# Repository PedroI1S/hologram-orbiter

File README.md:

# Hologram Orbiter

Display volumétrico por persistência de visão (POV) com três painéis de LEDs.
Ponto de projeto: raio médio **100 mm**, **1800 RPM**, 29 LEDs por painel e 180
colunas angulares (90 passagens por segundo; desempenho óptico depende de
firmware e ensaio).

**Versão vigente: v4.0 (14/11/2026)** — promove a base suspensa em paralelogramo
travável + aranha reforçada (`3.1-P.2`) e o motor **`AX-2810Q 750KV`** ao plano
principal. Os documentos e o pacote CAD da `v3.0` (base rígida + `A2212 920KV`)
foram arquivados em [`legado/v3.0/`](legado/v3.0/).

## Estado em 14/11/2026

> **PROVISÓRIO — não liberado para girar o rotor completo nem para fabricação
> definitiva dos painéis.**

- **CAD e física v4.0 regenerados (`69/69` critérios de aceitação):**
  - **Base suspensa em paralelogramo travável (PETG):** palco pendurado em 8
    hastes de `1,5 × 1,5 mm` (translação prevista em `4,38 Hz` / crítica
    `~263 RPM`), trava reversível 4 + 4 para operar em modo rígido e bandeja
    provisória para amortecimento viscoso com óleo de silicone `10 000 cSt`.
  - **Aranha reforçada (PETG):** aleta vertical em **D** + alma em perfil de asa
    invertido até o ombro (`r = 74 mm`), baia ampliada para **`Ø80/84 × 47 mm`**
    com prateleira em `Z = 28 mm` para futura placa própria.
  - **Motor e fixação (`AX-2810Q 750KV`):** medidas de bancada de `13/11/2026`
    incorporadas (assento serrilhado `Ø13` a `29 mm` da base, trecho liso
    `Ø4 × 5 mm` com bucha `Ø6`, rosca `M4 × 10`, porca `DIN 985 M4` + arruela
    `DIN 9021 M4`, furos de base em cruz `16/19 mm`, fios `Ø3,0 mm` em ganchos na
    torre, chapa `R01` com alívio `Ø11`). Réplica provisória `R01P` em PLA
    disponível até o corte em alumínio 2 mm.
- **Eletrônica e acionamento em bancada:**
  - **SPI Quad** montada ponto a ponto em placa perfurada
    ([`MONTAGEM-PONTO-A-PONTO.md`](eletronica/interface/MONTAGEM-PONTO-A-PONTO.md)),
    4 condutores por painel (`+5 V`, `GND`, `CLK`, `DATA`), em teste de bancada
    com [`firmware/teste-fitas-c3/`](firmware/teste-fitas-c3/).
  - **ESC + `AX-2810Q`:** gravados em `13/11/2026` (`Startup Power = 0,50`,
    `Demag = High`, `Brake on stop = On`; ver
    [`esc_blheli_s_2026-11-13/`](esc_blheli_s_2026-11-13/registro.md)). Sentido
    de giro anti-horário, calibração do pulso por tacômetro, grampo/resistor de
    descarga no barramento do ESC e ajustes de rampa no firmware da base ainda
    pendentes antes de girar com rotor.
- **Pendências principais antes de girar:** fechar medição da altura do corpo do
  `AX-2810Q` (`26 mm` de catálogo), imprimir peças e executar o ensaio de
  impacto **`C0`** da suspensão (modo travado e modo solto), reconciliar massa
  real pesada até o teto provisório de **`420 g`** e cumprir os bloqueadores do
  plano 04.

Os relatórios automáticos são a referência da execução atual do CAD:

- [Aceitação geométrica (69/69)](Hologram_Orbiter_v4/reports/ACEITACAO.md)
- [Validação, massas CAD e acionamento](Hologram_Orbiter_v4/reports/RELATORIO_VALIDACAO.md)
- [Cálculos reproduzíveis](Hologram_Orbiter_v4/reports/FISICA.json)
- [Revisões históricas (v3.0)](revisoes/LEIA-ME.md)

## Números de projeto (v4.0)

| Grandeza | Valor e condição |
|---|---|
| Rotação / velocidade angular | **1800 RPM** / 188,496 rad/s (30 rps, 90 Hz de imagem) |
| Cilindro de imagem | **Ø208 × 201 mm**, 29 LEDs × 180 colunas |
| Motor / acionamento | **AX-2810Q 750KV** (`R_ef = 0,225 Ω`, `Kt = 12,73 mN·m/A`) / **ESC LittleBee Spring 20A** |
| Corrente de regime prevista | **4,04 A** de fase (**3,62 A** melhor caso); **14,81 W** na fonte (`1,48 A` a 10 V, `1,23 A` a 12 V, `η_ESC = 95%`) |
| Temperatura prevista | **40,3 °C** (`37,8 °C` melhor caso) sob `Rth = 3,5 K/W`; limite `< 55 °C` (medir no Bloqueador B) |
| Fonte do ESC | **10–12 V** com limite de **30 A**; **grampo ou resistor de descarga obrigatório** (`Brake on stop = On`) |
| Perfil de partida (chute legado, não aprovado) | Chute de `1400 µs`: no modelo médio para o `AX-2810Q`, `16,37–19,65 A` de fase parado e pico de `1680 RPM` (10 V) / `1959 RPM` (12 V); excede Bloqueador D e exige revisão + rampa `≥ 300 RPM/s` pela crítica `~263 RPM` |
| Esticada a 2000 RPM | `4,99 A` / `20,63 W` / `47,0 °C` estimados; **não liberada** (3× próximo do modo ~89 Hz e > 20 W) |
| Massa do rotor | Teto provisório **420 g**; subtotal nominal **352,14 g** (reconciliar chicotes 4 fios e pesar) |
| Carga radial no painel | **158,1 N** a `44,5 g` (`159,9 N` no teto de `45 g`) |
| Energia cinética | **27,5–27,6 J** no rotor (`J = 1,55 g·m²` assumido); **7,9 J** (`18,9 m/s`) por painel solto |
| Desbalanceamento de referência | **8,4 g·mm** (ref. G6.3 a 1800 RPM; recalcular com massa pesada e balancear em 2 planos) |
| Modos da suspensão (estimativa `E = 1900 MPa`) | Translação **4,38 Hz** (**263 RPM**); *yaw* **12,66 Hz** (**759 RPM**, evitar banda `760–870 RPM`); combinado balanço+torre **89,3 Hz** (3× em `~1786 RPM`); balanço **105,2 Hz**; flambagem `36,3 N` |

A PCB KiCad de interface `r0.2` está preservada em [`eletronica/interface/`](eletronica/interface/README.md)
como referência de projeto; para o protótipo atual sem PCB fabricada, seguir o
roteiro de soldagem em perfboard [`MONTAGEM-PONTO-A-PONTO.md`](eletronica/interface/MONTAGEM-PONTO-A-PONTO.md).

## Documentos vigentes (v4.0)

| Uso | Arquivo |
|---|---|
| Cotas, geometria e memória de cálculo | [`01-ESPECIFICACAO-CAD-v4.0.md`](01-ESPECIFICACAO-CAD-v4.0.md) |
| Fases e portões `G0`–`G5` | [`02-PLANO-DE-PROJETO-v4.0.md`](02-PLANO-DE-PROJETO-v4.0.md) |
| Componentes, ferragens e instrumentos | [`03-LISTA-DE-COMPONENTES-v4.0.md`](03-LISTA-DE-COMPONENTES-v4.0.md) |
| Critérios físicos de aceite (`C0`, `A`–`E`) | [`04-PLANO-DE-ENSAIOS-v4.0.md`](04-PLANO-DE-ENSAIOS-v4.0.md) |
| Eletrônica **SPI Quad**, ESC e firmware | [`05-ESQUEMA-ELETRICO-v4.0.md`](05-ESQUEMA-ELETRICO-v4.0.md) |
| O que ainda falta | [`06-PENDENCIAS-ABERTAS-v4.0.md`](06-PENDENCIAS-ABERTAS-v4.0.md) |
| Medições, vocabulário e premissas | [`07-GLOSSARIO-E-PREMISSAS.md`](07-GLOSSARIO-E-PREMISSAS.md) |
| CAD, 16 STLs, DXF e guias de impressão/montagem | [`Hologram_Orbiter_v4/README.md`](Hologram_Orbiter_v4/README.md) |
| Firmware (base ESC + bancada SPI Quad C3) | [`firmware/README.md`](firmware/README.md) |
| Interface SPI Quad (perfboard e KiCad ref.) | [`eletronica/interface/README.md`](eletronica/interface/README.md) |
| Arquivo morto (`v3.0` e `v2.1`) | [`legado/LEIA-ME.md`](legado/LEIA-ME.md) |

Parâmetros do CAD governam cotas, a especificação governa requisitos e o plano
de ensaios governa aceite físico. Divergências devem ser corrigidas na fonte,
nunca escolhendo o número mais favorável. A [proposta e suas apresentações](proposta/README.md)
conservam os números históricos da proposta inicial.

Sentido de giro: **anti-horário visto de cima**; bordo de ataque em `+y` local.
Balança de `0,01 g`, contenção física, grampo no barramento do ESC, base
grampeada e operação remota são obrigatórios em ensaio.

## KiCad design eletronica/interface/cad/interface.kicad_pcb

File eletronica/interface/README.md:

# PCB de interface do rotor — r0.2

Placa de sinais em 15 × 20 mm, duas camadas, com montagem SMD no topo. Esta revisão implementa a arquitetura da proposta SPI quad lembrada pelo usuário: CLK comum, três DATA independentes e alimentação dos painéis em estrela externa. É um protótipo para orçamento e posterior ensaio, não uma eletrônica já qualificada em bancada.

## Arquivos para orçamento e revisão

- `fabricacao/gerbers/`: cobre, máscaras, serigrafias, pasta e furação exportados pelo KiCad.
- `fabricacao/Gerbers_Orbiter_r02.zip`: enviar ao campo de Gerber do fornecedor.
- `fabricacao/BOM.csv`: lista de compra e montagem, com MPN e quantidade por placa.
- `fabricacao/BOM-JLCPCB.csv`: correspondência de componentes para a JLCPCB.
- `fabricacao/PickAndPlace.csv`: coordenadas e rotações dos 17 SMDs.
- `fabricacao/mapa-fios.csv`: correspondência dos 19 pontos numerados com os sinais.
- `fabricacao/LEIA-ME-COTACAO.md`: requisitos para a fabricante, incluindo painelização e montagem.
- `fabricacao/Pacote_Orbiter_r02.zip`: conjunto para compartilhar com o fornecedor, incluindo fonte CAD e relatórios.
- `cad/interface.kicad_pro`, `cad/interface.kicad_sch`, `cad/interface.kicad_pcb`: projeto editável e bibliotecas locais.
- `reports/`: verificações, esquema exportado em SVG, PCB e molde físico 1:1.

A placa nua é cotada pelo Gerber; a montagem exige também BOM e Pick & Place. Conferir o preview do fornecedor, especialmente o pino 1 de U1 e as rotações. Códigos de componentes cadastrados não significam estoque reservado ou ausência de taxas adicionais.

## Circuito

| Função | Ligação |
|---|---|
| CLK comum | GPIO4 → U1 entrada 2 / saída 3 → R6, R10, R11 de 33 Ω → CLK de cada painel |
| DATA painel 1 | GPIO6 → U1 entrada 5 / saída 6 → R7 de 0 Ω → painel 1 |
| DATA painel 2 | GPIO5 → U1 entrada 9 / saída 8 → R12 de 0 Ω → painel 2 |
| DATA painel 3 | GPIO7 → U1 entrada 12 / saída 11 → R13 de 0 Ω → painel 3 |
| Habilitação do buffer | U1 pinos 1, 4, 10 e 13 ao GND |
| Repouso no reset | R1, R2, R8, R9: 10 kΩ de cada entrada digital ao GND |
| Alimentação de U1 | pino 14 em 5 V, pino 7 em GND; C1 100 nF junto ao CI e C2 1 µF local |
| Hall | A3144 externo em 5 V; R3 10 kΩ da saída a 3V3; leitura em GPIO3 |
| Bateria | R4 150 kΩ de VBAT_SW ao ADC; R5 47 kΩ ao GND; C3 100 nF ao GND; leitura em GPIO0 |

U1: SN74AHCT125DR, SOIC-14, entrada TTL e saída em 5 V. Não substituir por HC. Quatro canais usados; não sobram canais para clocks independentes. Um clock aciona três ramos com resistores série individuais, como na proposta local. Os resistores de DATA em 0 Ω permitem ajuste em bancada.

GPIO10 fica reservado para a quarta linha do periférico quad, sem fio na interface. As linhas DATA **não são unidas entre si**; cada painel recebe seus próprios bits. Saídas superiores das fitas ficam sem retorno à interface.

O ADC nominal vale 1,384 V a 5,8 V e 1,718 V a 7,2 V. Calibrar no firmware. O filtro deve permanecer próximo ao ADC eletricamente; manter o fio curto e acrescentar/reposicionar o capacitor junto ao C3 se a integração exigir. Este divisor mede a tensão e não desconecta a bateria.

## Fiação e alimentação

| Grupo funcional | Pinos |
|---|---|
| J1 — C3 | 1:5V; 2:GND; 3:3V3 vindo do C3; 4:GPIO4; 5:GPIO6; 6:GPIO3; 7:GPIO0; 8:GPIO5; 9:GPIO7 |
| J2 — Hall | 1:5V; 2:GND; 3:saída Hall |
| J3 — painel 1 | 1:CLK; 2:DATA painel 1 |
| J5 — painel 2 | 1:CLK; 2:DATA painel 2 |
| J6 — painel 3 | 1:CLK; 2:DATA painel 3 |
| J4 — bateria | 1:VBAT_SW, após chave/fusível e antes do buck |

Os grupos J representam pontos **distribuídos** pela placa, não headers comerciais contíguos. A numeração física 01–19 está na serigrafia inferior e no `mapa-fios.csv`. Os fios entram em furos metalizados de 0,5 mm; usar AWG28 nos sinais e na pequena alimentação da interface, conferindo o fio real. Fazer alívio mecânico. A ordem de J2 não representa a ordem dos terminais do sensor TO-92: conferir o componente real.

```
bateria + → fusível → chave → VBAT_SW → buck IN+
bateria - → GND comum / buck IN-
buck OUT+ → estrela 5V → painel 1+, painel 2+, painel 3+, C3 5V, interface 5V
buck OUT- → estrela GND → painel 1-, painel 2-, painel 3-, C3 GND, interface GND
1000 µF externo entre 5V e GND, no cubo
```

Cada painel recebe quatro fios: 5 V e GND pela distribuição de potência; CLK e seu DATA pela interface. Não passar os amperes dos LEDs pelas trilhas desta placa ou pelo fio fino de referência GND. O 5V do C3 recebe uma derivação externa própria; J1.1 não é um caminho de potência em série para o C3.

Chave, fusível, conector de balanceamento, buck e capacitor de 1000 µF continuam externos. É uma mudança de divisão física em relação à reserva antiga, que listava esses itens dentro de 15 × 20 sem modelos definidos. A acomodação e retenção desses componentes precisam ser verificadas no conjunto. Selecionar chave/fusível pela corrente DC real; não usar chave de sinal sem capacidade adequada para alimentar o buck. O buck real ainda precisa de qualificação ao longo da descarga da bateria.

> **Sem PCB:** a placa r0.2 não será fabricada. Para a montagem soldada à mão,
> com apenas o U1 já fixado, seguir [MONTAGEM-PONTO-A-PONTO.md](MONTAGEM-PONTO-A-PONTO.md)
> (mesmo circuito, com o envelope, o peso e a sequência de solda revistos).

## Encaixe

Centro no rotor `(27; 5) mm`, com cantos `(19,5; -5)` a `(34,5; 15)`. Na **v4.0**, a baia foi ampliada para **`Ø80` interno (`r = 40 mm`) / `Ø84` externo × `47 mm`**, deixando folga radial nominal de **`2,38 mm`** até o canto mais externo (`r = 37,62 mm`). *(Nos relatórios preservados da revisão `r0.2` / `v3.0`, como `reports/geometry.json`, a referência anterior era `r = 39 mm` / `1,38 mm`; o diagrama `reports/encaixe-baia.svg` já foi atualizado para `Ø80 mm`. Acima do berço da bateria, a prateleira em `Z = 28 mm` reserva espaço para uma eventual placa própria futura.)*

Furos de `2,2 mm` em `(2; 2)`, `(13; 2)`, `(13; 18)`, `(2; 18)` relativos ao canto da PCB. São os centros dos quatro pilares existentes no CAD. Cabeças até `Ø3,5 mm`, sem arruelas maiores; confirmar rosca e retenção nos pilares reais. A área das cabeças foi reservada também contra cobre/trilhas.

Face inferior da PCB a `Z = 6 mm`. Com FR4 de `1,6 mm` e SOIC de até aproximadamente `1,75 mm`, a pilha eletrônica fica abaixo do envelope anterior de `8 mm`. Fios e soldas não estão incluídos nessa comprovação nominal. Manter as pontas inferiores curtas para não obstruir chicotes sob a placa. O molde `reports/molde-1-para-1.svg` deve ser impresso a 100%; conferir a barra de `50 mm` antes de testar.

## Verificação e limites

Os resultados da revisão `r0.2` ficam em [`reports/VALIDACAO.md`](reports/VALIDACAO.md): zero violações ERC/DRC, zero conexões abertas e zero divergências de paridade no KiCad 10.0.7. Há conferência independente de geometria, continuidade entre camadas, folgas de cobre e equivalência de pinos entre tabela elétrica, esquemático e PCB. O DRC/ERC do KiCad e os arquivos exportados são verificados antes do empacotamento.

Isso não demonstra integridade dos sinais nos fios reais. Com rotor parado, verificar três padrões independentes, ordem de bits do SPI quad, clock na entrada das três fitas, funcionamento do Hall e leitura da bateria (ver [`firmware/teste-fitas-c3/`](../../firmware/teste-fitas-c3/)). Começar com alimentação limitada e obedecer ao teto provisório de corrente/brilho do esquema 05. Se um driver de clock para três ramos não bastar, será necessário rever hardware/clock; esta placa não reserva um segundo CI.

Ao programar o C3, confirmar o circuito da Super Mini real antes de alimentar simultaneamente por USB e buck; evitar realimentar fontes. Mudanças de massa/fiação exigem nova pesagem e balanceamento. Nenhuma pendência mecânica do rotor é encerrada pela interface.

## Reprodução

Os scripts em `scripts/` geram e verificam o projeto KiCad; as ferramentas são KiCad CLI, Python com `sexpdata`/`shapely` e Freerouting 2.1.0 em Java 21. O gerador de posicionamento não preserva edições manuais: usar o CAD final (`Hologram_Orbiter_v4/CAD/parameters.json`) como fonte ao alterar a placa e regenerar as saídas da revisão modificada.

## Referências

- [Esquema vigente (v4.0)](../../05-ESQUEMA-ELETRICO-v4.0.md): topologia SPI Quad vigente (4 fios por painel), alimentação, pinagem e requisitos de ensaio.
- [Montagem ponto a ponto (perfboard ativa)](MONTAGEM-PONTO-A-PONTO.md): roteiro prático em execução para o protótipo sem PCB fabricada.
- [Proposta SPI quad](../../revisoes/2026-09-21-PROPOSTA-SPI-QUAD.md): proposta original adotada na revisão e promovida na v4.0.
- [TI — SN74AHCT125](https://www.ti.com/lit/ds/symlink/sn74ahct125.pdf): pinagem, níveis e encapsulamento.
- [Espressif — checklist C3](https://docs.espressif.com/projects/esp-hardware-design-guidelines/en/latest/esp32c3/schematic-checklist.html): recomendação de filtro no ADC.

Para reexportar o CAD final sem regenerar o posicionamento: `python scripts/export_manufacturing.py --kicad-cli /caminho/kicad-cli` (KiCad 10 e dependências de `scripts/requirements.txt`).

Revisão de compra em 30/10: [BOM otimizada para JLCPCB](fabricacao/BOM-JLCPCB-otimizada.csv), com seis grupos Basic e substituto X7R 25 V para C2. Ver [substituições e consulta de estoque](reports/REVISAO-BOM-JLCPCB.md). Gerbers e Pick & Place permanecem os da PCB r0.2.

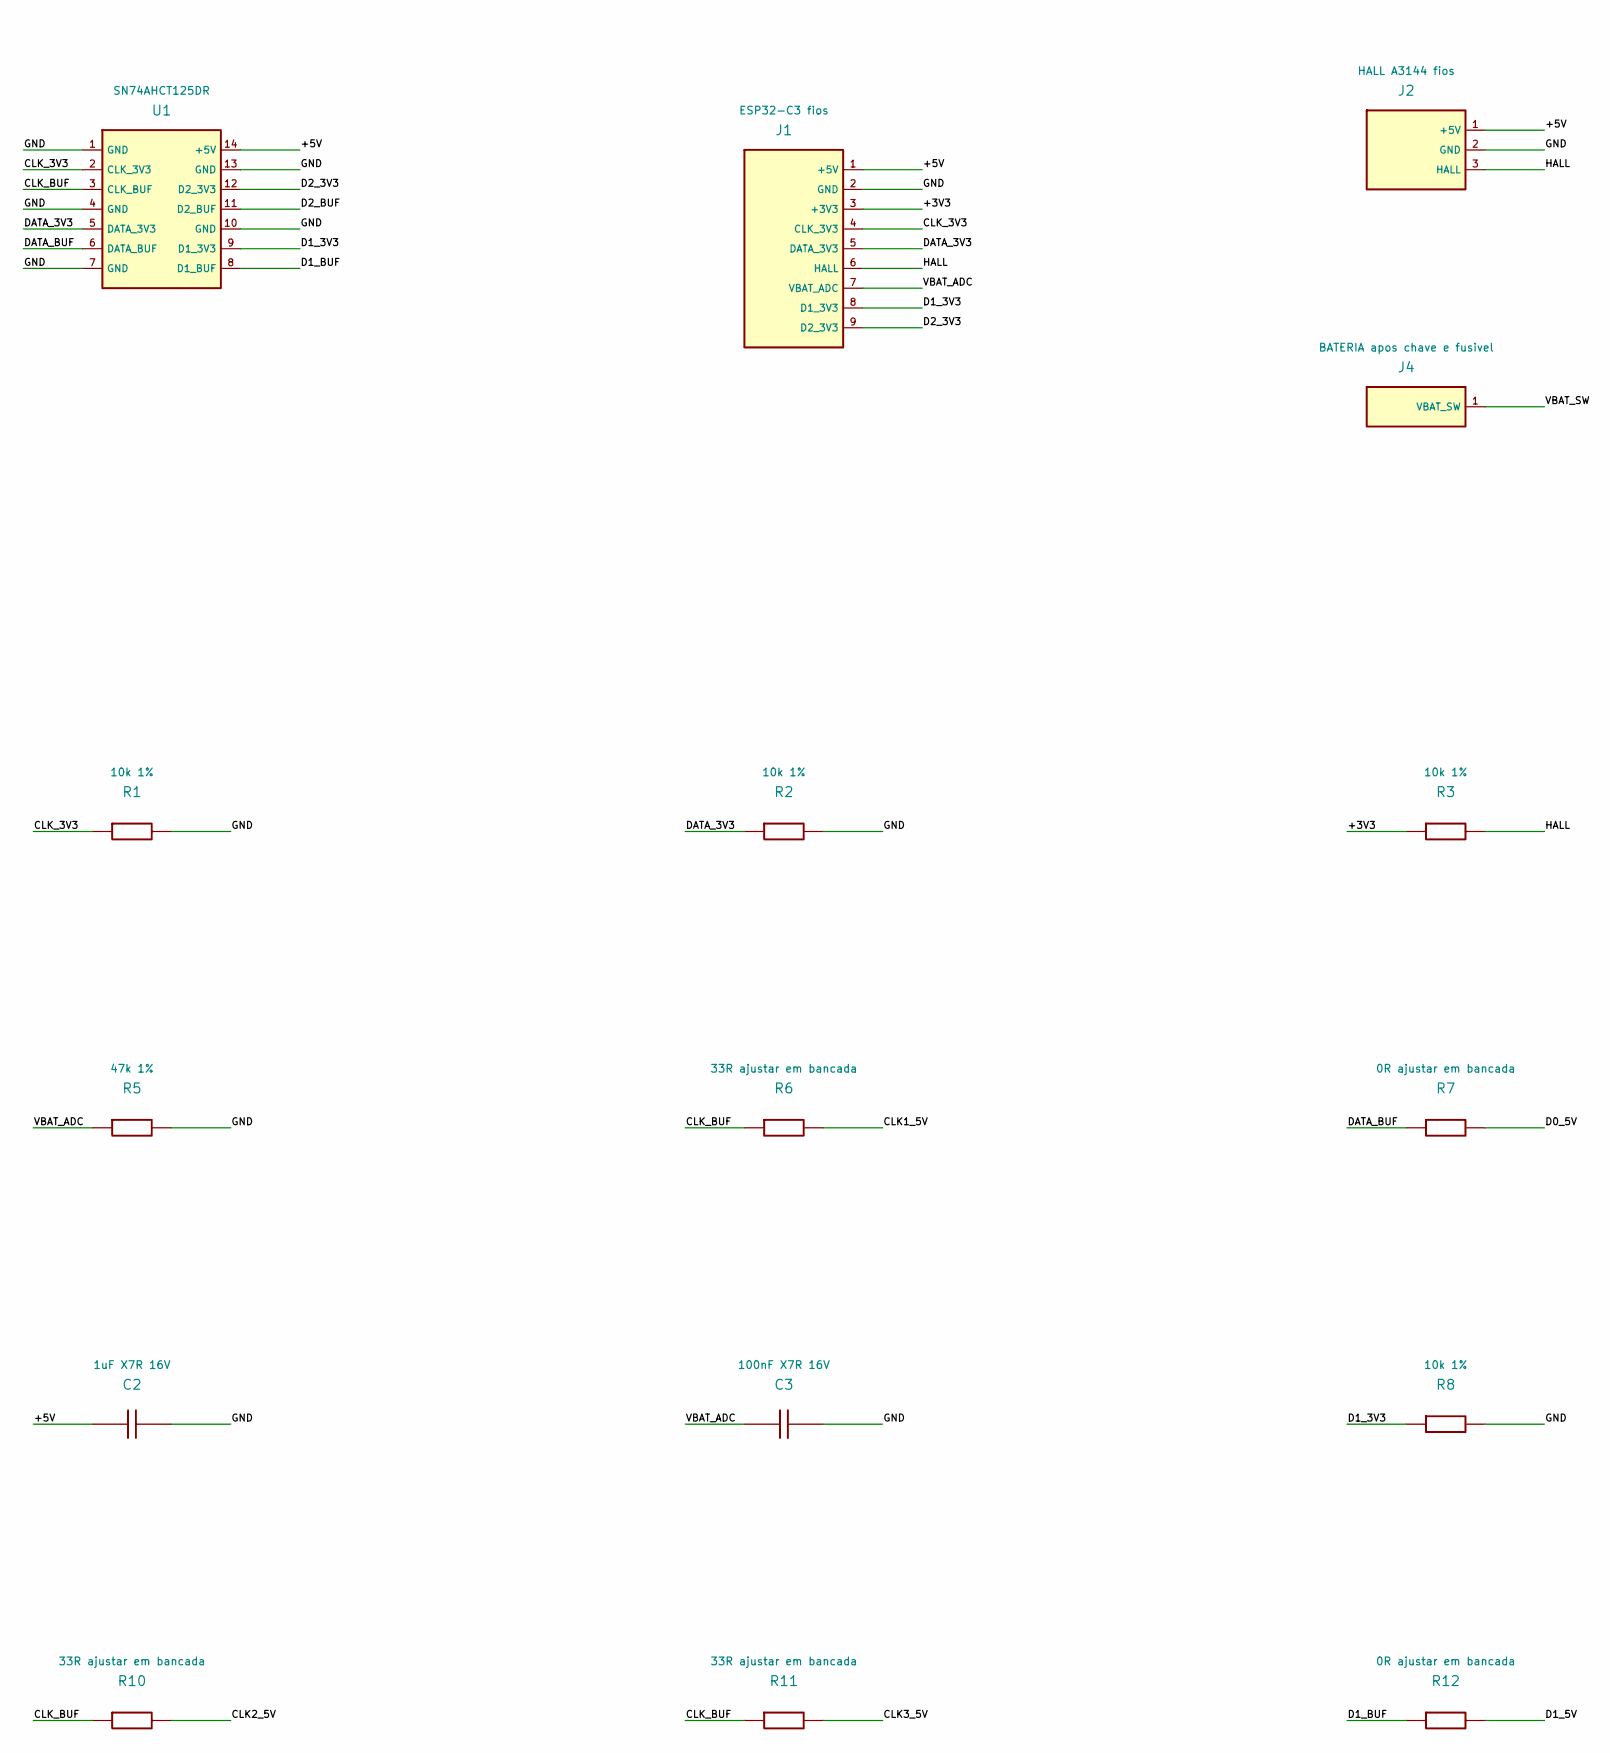
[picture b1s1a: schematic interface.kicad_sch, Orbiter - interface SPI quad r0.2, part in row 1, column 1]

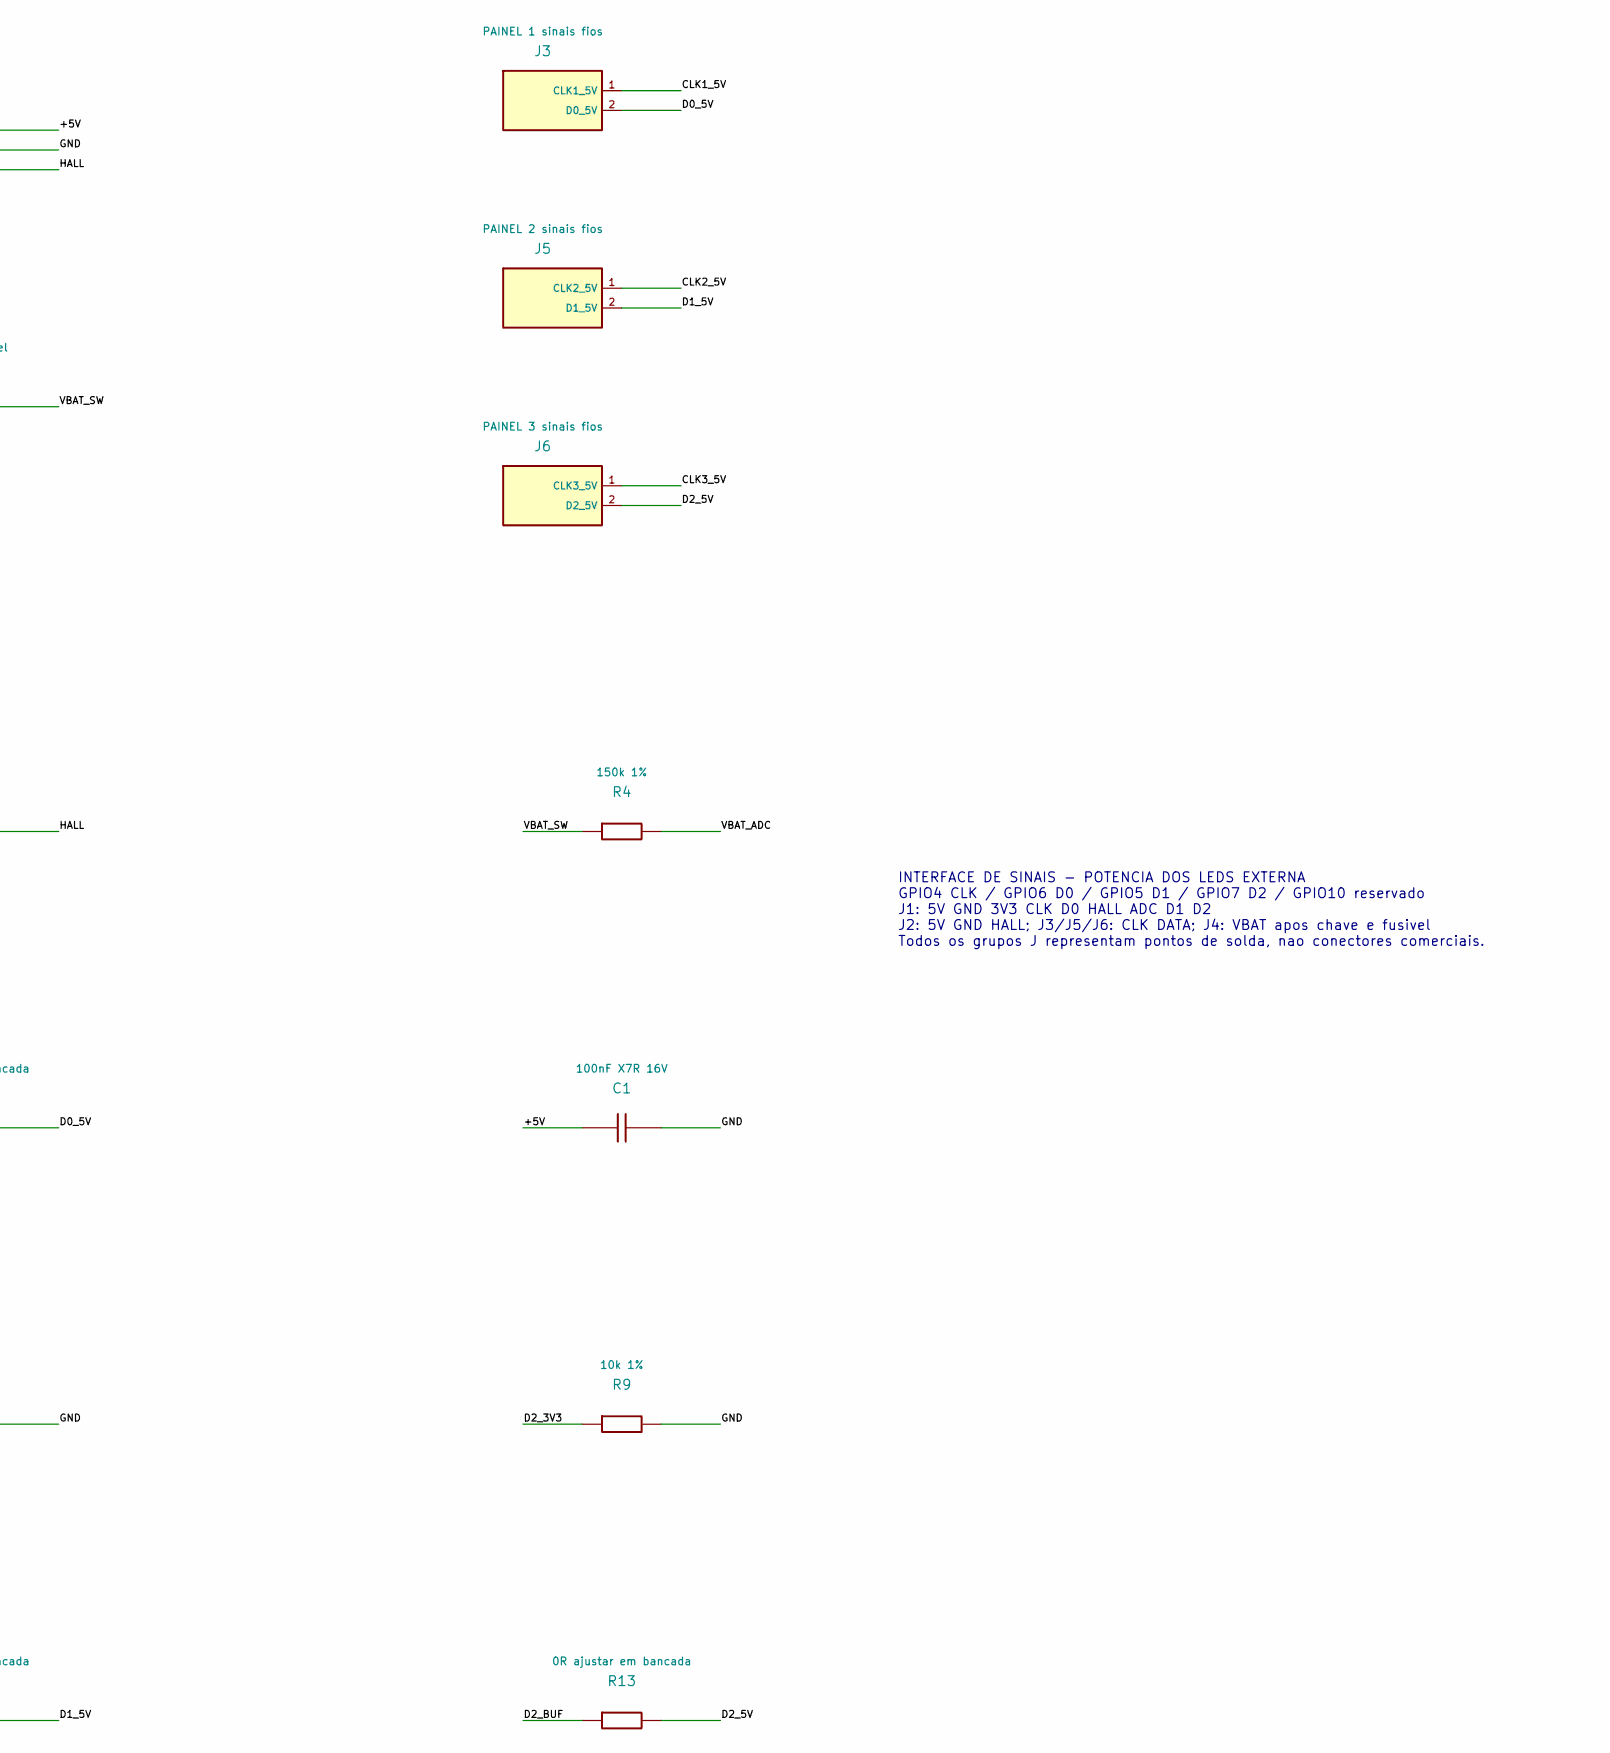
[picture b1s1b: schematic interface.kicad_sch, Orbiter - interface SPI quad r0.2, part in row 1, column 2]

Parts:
C1: 100nF X7R 16V; C1
C2: 1uF X7R 16V; C2
C3: 100nF X7R 16V; C3
J1: ESP32-C3 fios; J1
J2: HALL A3144 fios; J2
J3: PAINEL 1 sinais fios; J3
J4: BATERIA apos chave e fusivel; J4
J5: PAINEL 2 sinais fios; J5
J6: PAINEL 3 sinais fios; J6
R1: 10k 1%; R1
R2: 10k 1%; R2
R3: 10k 1%; R3
R4: 150k 1%; R4
R5: 47k 1%; R5
R6: 33R ajustar em bancada; R6
R7: 0R ajustar em bancada; R7
R8: 10k 1%; R8
R9: 10k 1%; R9
R10: 33R ajustar em bancada; R10
R11: 33R ajustar em bancada; R11
R12: 0R ajustar em bancada; R12
R13: 0R ajustar em bancada; R13
U1: SN74AHCT125DR; U1

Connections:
/+3V3: J1.3 (+3V3), R3.1 (+3V3)
/+5V: C1.1 (+5V), C2.1 (+5V), J1.1 (+5V), J2.1 (+5V), U1.14 (+5V)
/CLK1_5V: J3.1 (CLK1_5V), R6.2 (CLK1_5V)
/CLK2_5V: J5.1 (CLK2_5V), R10.2 (CLK2_5V)
/CLK3_5V: J6.1 (CLK3_5V), R11.2 (CLK3_5V)
/CLK_3V3: J1.4 (CLK_3V3), R1.1 (CLK_3V3), U1.2 (CLK_3V3)
/CLK_BUF: R6.1 (CLK_BUF), R10.1 (CLK_BUF), R11.1 (CLK_BUF), U1.3 (CLK_BUF)
/D0_5V: J3.2 (D0_5V), R7.2 (D0_5V)
/D1_3V3: J1.8 (D1_3V3), R8.1 (D1_3V3), U1.9 (D1_3V3)
/D1_5V: J5.2 (D1_5V), R12.2 (D1_5V)
/D1_BUF: R12.1 (D1_BUF), U1.8 (D1_BUF)
/D2_3V3: J1.9 (D2_3V3), R9.1 (D2_3V3), U1.12 (D2_3V3)
/D2_5V: J6.2 (D2_5V), R13.2 (D2_5V)
/D2_BUF: R13.1 (D2_BUF), U1.11 (D2_BUF)
/DATA_3V3: J1.5 (DATA_3V3), R2.1 (DATA_3V3), U1.5 (DATA_3V3)
/DATA_BUF: R7.1 (DATA_BUF), U1.6 (DATA_BUF)
/GND: C1.2 (GND), C2.2 (GND), C3.2 (GND), J1.2 (GND), J2.2 (GND), R1.2 (GND), R2.2 (GND), R5.2 (GND), R8.2 (GND), R9.2 (GND), U1.1 (GND), U1.4 (GND), U1.7 (GND), U1.10 (GND), U1.13 (GND)
/HALL: J1.6 (HALL), J2.3 (HALL), R3.2 (HALL)
/VBAT_ADC: C3.1 (VBAT_ADC), J1.7 (VBAT_ADC), R4.2 (VBAT_ADC), R5.1 (VBAT_ADC)
/VBAT_SW: J4.1, R4.1 (VBAT_SW)

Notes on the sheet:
INTERFACE DE SINAIS - POTENCIA DOS LEDS EXTERNA GPIO4 CLK / GPIO6 D0 / GPIO5 D1 / GPIO7 D2 / GPIO10 reservado J1: 5V GND 3V3 CLK D0 HALL ADC D1 D2 J2: 5V GND HALL; J3/J5/J6: CLK DATA; J4: VBAT apos chave e fusivel Todos os grupos J representam pontos de solda, nao conectores comerciais.

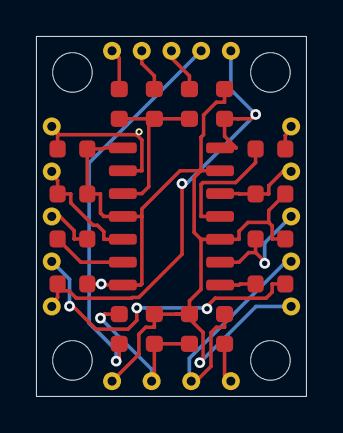
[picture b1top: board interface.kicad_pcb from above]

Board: 2 copper layers, 15.0 x 20.0 mm, 27 parts (0 on the bottom side), 20 nets.

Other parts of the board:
H1: H1
H2: H2
H3: H3
H4: H4

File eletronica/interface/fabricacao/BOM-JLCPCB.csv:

Comment,Designator,Footprint,LCSC Part #
5V quad TTL buffer,U1,SOIC-14,C155176
10k 1% 0.1W,"R1,R2,R3,R8,R9",0603,C25804
150k 1% 0.1W,R4,0603,C22807
47k 1% 0.1W,R5,0603,C25819
33R 1% 0.1W,"R6,R10,R11",0603,C23140
0R jumper,"R7,R12,R13",0603,C21189
100nF 50V X7R 10%,"C1,C3",0603,C14663
1uF 25V X7R 10%,C2,0603,C5972986
